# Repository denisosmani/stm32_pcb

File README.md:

# STM32 Custom Development Board

A custom-designed STM32F103C8T6 development board featuring essential components for easy programming, communication, and expansion.

## Features
- USB Micro-B port for power and communication
- AMS1117-3.3 voltage regulator
- BOOT0 switch for programming mode selection
- 16 MHz external crystal oscillator
- SWD 4-pin header for programming/debugging
- I2C and UART pin headers for peripheral connections
- Compact and robust PCB design

## Hardware Overview

### Schematic View
The schematic includes the STM32F103C8T6 microcontroller, voltage regulation, USB interface, programming headers, and peripheral connectors.

### PCB Layout and Routing
The PCB is routed to ensure stable operation, minimal noise, and good power distribution.

### 3D PCB View
A realistic 3D view of the assembled PCB.

## Components
- **Microcontroller:** STM32F103C8T6
- **Voltage Regulator:** AMS1117-3.3
- **Clock:** 16 MHz Crystal Oscillator
- **Communication:** USB Micro-B port, I2C header, UART header
- **Programming:** SWDIO 4-pin header, BOOT0 switch for mode selection

### Programming the Board
- Use an SWD programmer (such as ST-Link V2) connected to the SWDIO 4-pin header.
- Set the BOOT0 switch appropriately when flashing firmware:
  - **Programming mode:** BOOT0 = HIGH
  - **Normal operation:** BOOT0 = LOW

### Powering the Board
- Power can be provided through the USB Micro-B port or an external 5V supply.

### Pin Headers
- **I2C Header:** Connect external I2C peripherals.
- **UART Header:** Debug and communicate with other devices over UART.

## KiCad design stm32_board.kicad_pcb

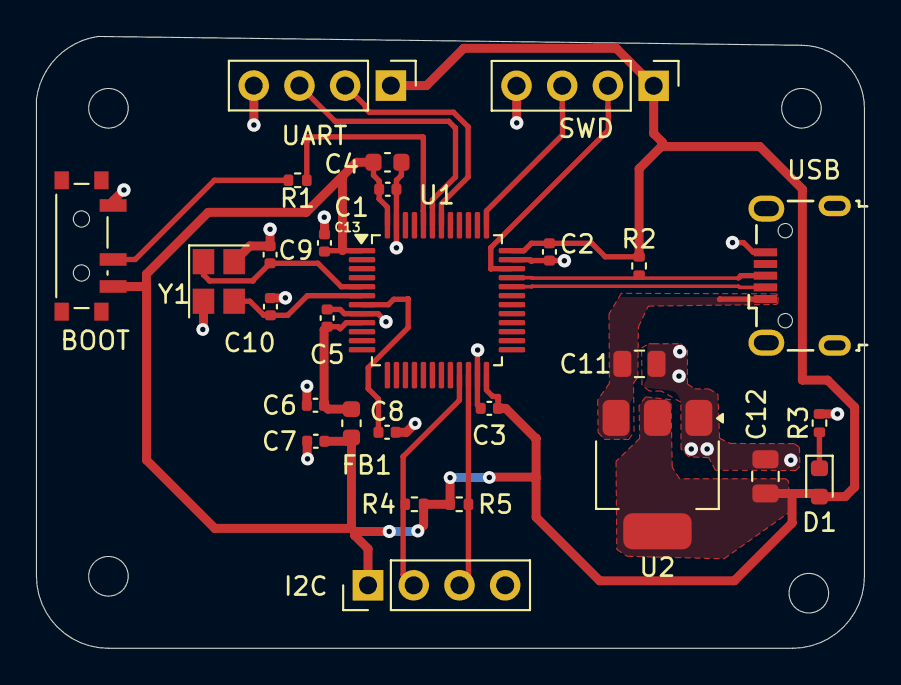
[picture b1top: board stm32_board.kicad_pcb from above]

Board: 2 copper layers, 46.0 x 34.0 mm, 32 parts (0 on the bottom side), 18 nets.

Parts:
BOOT: SW_SPDT; SW_SPDT_PCM12
C1, C2, C3, C8, C13: 100n; C_0402_1005Metric
C4: 10u; C_0603_1608Metric
C5: 10n; C_0402_1005Metric
C6, C7: 1u; C_0402_1005Metric
C9, C10: 10p; C_0402_1005Metric
C11, C12: 22u; C_0805_2012Metric
D1: LED; LED_0603_1608Metric
FB1: 120R; L_0603_1608Metric
H1, H2, H3, H4: MountingHole; MountingHole_2.2mm_M2
I2C: Conn_01x04_Pin; PinHeader_1x04_P2.54mm_Vertical
R1: 10k; R_0402_1005Metric
R2, R3, R4, R5: 1k5; R_0402_1005Metric
SWD: Conn_01x04_Pin; PinHeader_1x04_P2.54mm_Vertical
U1: STM32F103C8T6; LQFP-48_7x7mm_P0.5mm
U2: AMS1117-3.3; SOT-223-3_TabPin2
UART: Conn_01x04_Pin; PinHeader_1x04_P2.54mm_Vertical
USB: USB_B_Micro; USB_Micro-B_Wuerth_629105150521
Y1: 16MHz; Crystal_SMD_3225-4Pin_3.2x2.5mm

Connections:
+3.3V: BOOT.3 (C), C1.1, C2.1, C3.1, C4.1, C7.1, C12.1, C13.1, D1.2 (A), FB1.2, I2C.1, R2.1, R4.1, R5.1, SWD.1, U1.1 (VBAT), U1.24 (VDD), U1.36 (VDD), U1.48 (VDD), U2.2 (VO), UART.1
+3.3VA: C5.1, C6.1, FB1.1, U1.9 (VDDA)
/BOOT0: R1.2, U1.44 (BOOT0)
/HSE_IN: C9.1, U1.5 (PD0), Y1.1
/HSE_OUT: C10.1, U1.6 (PD1), Y1.3
/I2C2_SCL: I2C.2, R4.2, U1.21 (PB10)
/I2C2_SDA: I2C.3, R5.2, U1.22 (PB11)
/NRST: C8.1, U1.7 (NRST)
/PWR_LED_K: D1.1 (K), R3.1
/SWCLK: SWD.3, U1.37 (PA14)
/SWDIO: SWD.2, U1.34 (PA13)
/SW_BOOT0: BOOT.2 (B), R1.1
/USART1_RX: U1.43 (PB7), UART.3
/USART1_TX: U1.42 (PB6), UART.2
/USB_D+: R2.2, U1.33 (PA12), USB.3 (D+)
/USB_D-: U1.32 (PA11), USB.2 (D-)
GND: BOOT.1 (A), C1.2, C2.2, C3.2, C4.2, C5.2, C6.2, C7.2, C8.2, C9.2, C10.2, C11.2, C12.2, C13.2, I2C.4, R3.2, SWD.4, U1.8 (VSSA), U1.23 (VSS), U1.35 (VSS), U1.47 (VSS), U2.1 (GND), UART.4, USB.5 (GND), Y1.2, Y1.4
VBUS: C11.1, U2.3 (VI), USB.1 (VBUS)

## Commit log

2025-04-26 stm32 pcb design
